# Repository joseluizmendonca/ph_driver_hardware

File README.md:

## Peak-and-Hold / Saturation Injector Driver (Hardware)

This repository contains the hardware for an automotive injector driver board that supports both Peak-and-Hold (PH) and Saturation drive modes. It's intended for flexible use across different injector types and engine setups.

The project is a simplified/ downtuned version of the sytem that I designed for my bachelors thesis for driving methanol injectors which would be overkill for most aplications, and is not yet public

Design files are in `src/`.

## Photos / Renders

Below are images from the board.

## Features

- Supports both injector drive strategies:
	- Peak-and-Hold (PH) for low-impedance injectors
	- Saturation for high-impedance injectors
- Works with both high-impedance and low-impedance injectors
- Stackable: multiple boards can be placed one on top of another to drive more injectors
- KiCad project files included (`.kicad_sch`, `.kicad_pcb`) under `src/`
- Max switching frequency: under test (TBD)
- Proven setup: tested on a Weber 2-cylinder engine with ~12 Ω injectors, and also on low impedance injectors on a testbench
- Cost-conscious design: uses a common N‑channel MOSFET with discrete flyback/clamp diodes to manage inductive kickback, avoiding expensive automotive‑rated ICs where practical
- MCP1406 MOSFET gate driver for fast gate charge delivery and sharp turn‑on/turn‑off
- Adjustable flyback clamp: injector shutoff speed can be tuned by changing the output‑side Zener diode value

## Peak-and-Hold vs. Saturation (Quick primer)

Automotive injectors are solenoid valves. To open quickly and control heating, there are two common drive strategies:

- Peak-and-Hold (PH):
	- Typically used with low-impedance injectors (e.g., 1–3 Ω).
	- A high initial current “peak” is applied to open the injector rapidly, then the current is reduced to a lower “hold” level to keep it open while minimizing power dissipation and coil heating.
	- Requires current control (sensing + limiting) and a fast driver.

- Saturation:
	- Typically used with high-impedance injectors (e.g., 12–16 Ω).
	- The driver applies battery voltage and lets the current rise to a safe level dictated by the injector’s resistance. Simpler electronics, slower opening than PH for low-impedance coils but appropriate for high-impedance parts.
	- Current limiting is less complex; thermal stress is inherently lower due to higher coil resistance.

This board is designed to accommodate both approaches so you can pair the drive mode with your injector type. Use PH for low-impedance injectors to achieve fast opening while controlling heat, and use saturation mode for high-impedance injectors for a simpler setup.

## Design goals (cost and availability)

The main goal was to build a robust injector driver without relying on expensive, automotive‑rated monolithic components. Instead, the design:

- Uses a common N‑channel power MOSFET as the switching element
- Protects it using discrete diodes and a Zener clamp against the solenoid’s inductive kickback
- Adds a dedicated MOSFET gate driver (MCP1406) to ensure fast and repeatable switching

This keeps the BOM accessible and cost‑effective while maintaining performance suitable for practical engine control setups.

## Inductive kickback, clamping, and shutoff time

When turning the injector off, the coil’s stored energy forces current to continue flowing. A clamp network provides a safe path and defines the voltage across the coil, which sets the current decay rate. In simple terms, di/dt ≈ Vclamp / L, so a higher clamp voltage yields faster current fall and a quicker injector shutoff.

- Adjustable clamp via Zener: You can change the Zener diode on the output side to set the clamp voltage.
- Trade‑offs:
	- Higher clamp voltage → faster shutoff time, but the MOSFET must withstand a higher VDS during the event and the clamp network must absorb more energy.
	- Lower clamp voltage → reduced MOSFET voltage stress and a “safer” environment for the switch, but slower shutoff time (longer tail current).

Choose the Zener rating considering MOSFET VDS limits, injector L/R, energy dissipation in the clamp path, and thermal margins. The included simulations and schematics in `src/` show the intended topology. The BOM references common Zener parts (for example, 1N5338B family) that can be swapped to suit your target clamp level.

## Falstad demos (kickback concept)

Small interactive simulations demonstrating the kickback clamp concept are available on Falstad:

- [Single diode vs Zener clamp](https://www.falstad.com/circuit/circuitjs.html?ctz=CQAgjCAMB0l3BWK0BsB2AnADgEwI5gMw6SFZYQAsOISlhtApgLRhgBQANiMeGDb140YkCMwzQ0bBCkKEMOQmkUJCLElHYATPjQwpdISlhA0tjAGYBDAK6cALu0KUQFgO5aATgHsADgB0ARxgsSAMIMEkwegQcCgUKeBwWNChTWHhMrMgsFw0OAC9DZl42ARoady8-IJCw9jceGjLDFsgGw31W-k1G3mZjYsH2xpaBkzHeEcNSnuH2ADcQZhQXQZWXEuE0ykhwbb2YBHYAc2XVoxMNkAvDjuut8835xofB-vmAZyaZit20iDWTifRinH44f5CchpdqeH6CGjjAE4dhw+jlIwfEx7fhg9Gmf74uLYzTffEtIn-HGuKzA0F9QgGJH4pHTORMwSM5bzM7sy48Lm3TRLPnvLmPQ5GHEHZDHRrknoIHptbS0HoXJXNAxmSy2BxcTHNOYI0zIUS0aCUagYMCxFAIfDkDAIFhgDC9Q3ckyar0en0tH23Dr+gw+1nsbw8U17XYYd3-SIGPYCHgR0wVHaQOOmHGocCmnACdhAA)

- [FET ringing mitigation](https://www.falstad.com/circuit/circuitjs.html?ctz=CQAgjCAMB0l3BWEDoBYEE4AcYFwMz5iqoBMqIZyl+yApgLRhgBQAbuBqSIQGyfdSkLJWq9I4bhOnQELAGYhSWEUJH5eq4T25hZUWKRYAnAUu3KtIiRlSQWAYyUrwAdn6XJIimEbMQTKSw2LjMkBiuWBjRrgZwEDCsADY8ml6p3tZxEAww8HAYkORwJFh2GGDYUiwAJpSoIszcpSC8FNw1dPIAhgCuSQAuLABe9SJM-C0NSiCdPf0DDMN0AHZ0xiwA7s5WO2789tueanvFUCwA5mZ81whS51ca6kIZPHdQ59tPSuSv+C+HPZgZSvYHWLagkEtMGfMbgYFwmGA74Mf5w1HVbYtDHosAHCFTbzTNrnDikVzcEnk7gTD4SOySOkGORXamtdoUkBYaSwtm0vlowEC7gowUmV4477TCTAiHfSoitJIlgAe3AtAo9PCGHMBiyulo+BY+FUIAAYgkPmB4AEIAAlOgAZwAlo6Bt0Vg46CwgA)

## Scaling up (stacking boards)

The board is stackable: you can assemble and stack multiple boards to drive a higher number of injectors. Ensure proper power distribution, grounding, and cooling when scaling up, and verify your controller’s channel count and timing strategy.

## Assembly notes

Due to the size of the power planes attached to the main MOSFET, hand soldering those components is not recommended—the planes wick heat and make it difficult to achieve proper wetting.

Recommended approaches:

- Hot plate or reflow oven for consistent thermal profile
- Fabricator assembly (e.g., JLCPCB). Assembly files are included in `src/` to support turnkey assembly

If you must rework by hand, preheat the board, use ample flux, and use a proper soldering iron.

## SMD MOSFET thermal note

The latest revision uses surface‑mount MOSFETs. Thermal vias were added under the main drain pad to spread heat into inner and bottom copper. In bench tests so far, device temperatures remained fully acceptable, so external heatsinks are not required for typical operating conditions.

## Status

- Max switching frequency: still under test.
- Tested on a Weber two-cylinder engine using injectors of approximately 12 Ω impedance.

## Directory

- `src/` – KiCad schematics/PCB, libraries, production assets.
- `3d_render/` – Blender/KiCad 3D assets for visuals.
- `pics/` – Screenshots and renders used in this README.

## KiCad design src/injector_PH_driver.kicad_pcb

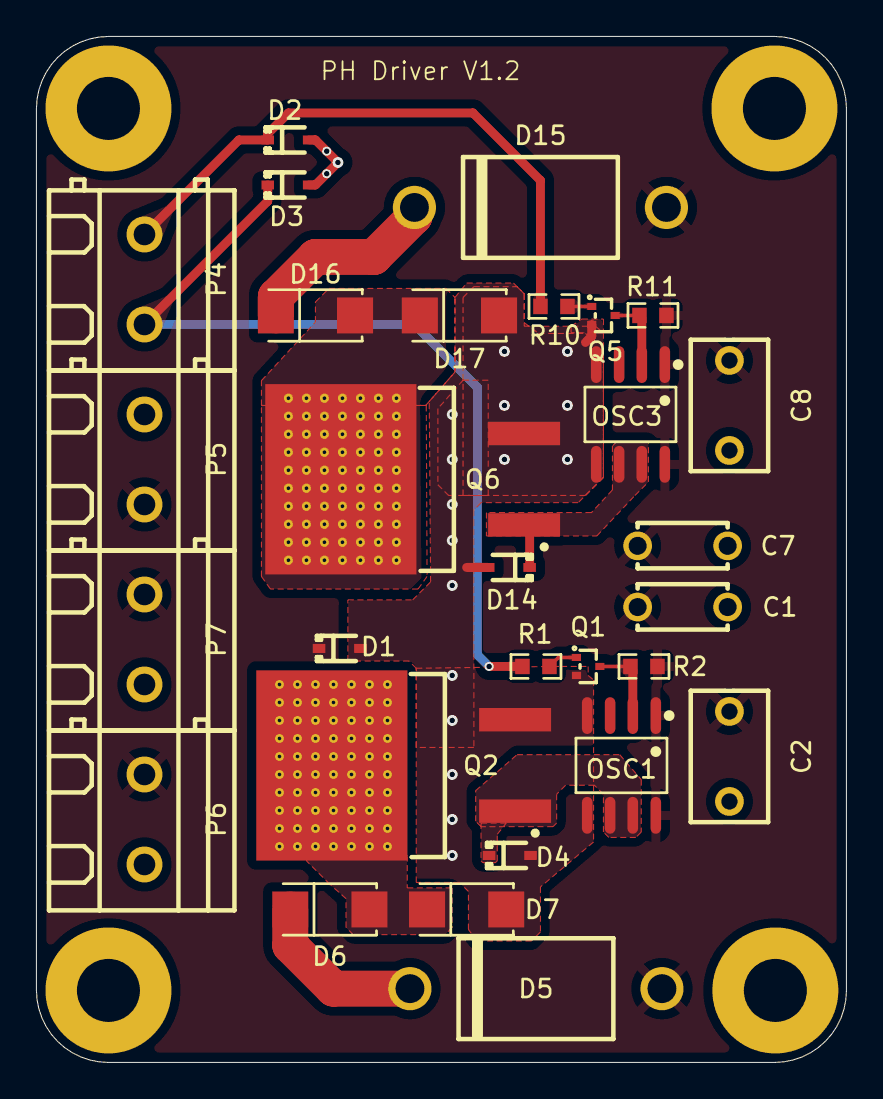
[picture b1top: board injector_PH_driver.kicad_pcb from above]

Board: 2 copper layers, 45.0 x 57.0 mm, 33 parts (0 on the bottom side), 14 nets.

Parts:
C1, C7: CC1H104MC1FD3F6C10MF; CAP-TH_L5.0-W2.5-P5.00-D1.0
C2, C8: B32529C0105J289; CAP-TH_L7.3-W4.5-P5.00-D0.5
D1, D2, D3, D4, D14: DF2S6P2FU,H3F; USC_L1.7-W1.3-LS2.5-R-RD
D5, D15: 1N5338BRLG; DO-27_BD5.2-L8.9-P12.90-D1.5-RD
D6, D7, D16, D17: MRA4007T3G; SMA_L4.3-W2.6-LS5.2-RD
H1, H2, H3, H4: MountingHole; MountingHole_3.5mm_Pad
OSC1, OSC3: MCP1406-E/P; SOIC-8_L4.9-W3.9-P1.27-LS6.0-BL
P4, P5, P6, P7: WJ128V-5.0-2P; CONN-TH_2P-P5.00_WJ128V-5.0-2P
Q1, Q5: BC847BT-7-F; SOT-523-3_L1.6-W0.8-P1.00-LS1.6-BR
Q2, Q6: IRFZ44NSTRLPBF; TO-263-2_L10.0-W9.1-P5.08-LS15.2-TL
R1, R2, R10, R11: r=10k; R0603

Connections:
/Drv1: D3.2 (K), P4.2, R1.2
/Drv2: D2.2 (K), P4.1, R10.2
/Inj1-: D6.2 (A), D7.1 (C), P6.2, Q2.4 (D)
/Inj2-: D16.2 (A), D17.1 (C), P7.2, Q6.4 (D)
/driver1/mosfet_power: D4.2 (K), OSC1.6 (OUT), OSC1.7 (OUT), Q2.1 (G)
/driver2/mosfet_power: D14.2 (K), OSC3.6 (OUT), OSC3.7 (OUT), Q6.1 (G)
GND: C1.1, C2.2, C7.1, C8.2, D1.1 (A), D2.1 (A), D3.1 (A), D4.1 (A), D7.2 (A), D14.1 (A), D17.2 (A), OSC1.4 (GND), OSC1.5 (GND), OSC3.4 (GND), OSC3.5 (GND), P5.1, Q1.2 (E), Q2.3 (S), Q5.2 (E), Q6.3 (S)
unnamed: D5.1 (K), D6.1 (C)
unnamed: D15.1 (K), D16.1 (C)
unnamed: OSC1.2 (IN), Q1.3 (C), R2.2
unnamed: OSC3.2 (IN), Q5.3 (C), R11.2
unnamed: Q1.1 (B), R1.1
unnamed: Q5.1 (B), R10.1
VCC: C1.2, C2.1, C7.2, C8.1, D1.2 (K), D5.2 (A), D15.2 (A), OSC1.1 (VDD), OSC1.8 (VDD), OSC3.1 (VDD), OSC3.8 (VDD), P5.2, P6.1, P7.1, R2.1, R11.1

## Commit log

2025-10-15 Added: initial port
2025-10-19 Added: rough outline
2025-10-19 Finished routing
2025-10-19 Updated: ground plane couplling vias
2025-10-19 Updated: injector 1 input trace
2025-10-19 Added. name and version
2025-10-19 Added: 3d export of v1.2
2025-10-19 Added: renders
2025-10-19 Added: more temp pictures
2025-10-19 Updated: README
2025-10-20 Added: final renders
2025-10-20 Updated: small wording change
